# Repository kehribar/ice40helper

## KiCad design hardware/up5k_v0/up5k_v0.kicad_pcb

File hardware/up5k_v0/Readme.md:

# UP5K Development Board

TODO: Add details ...

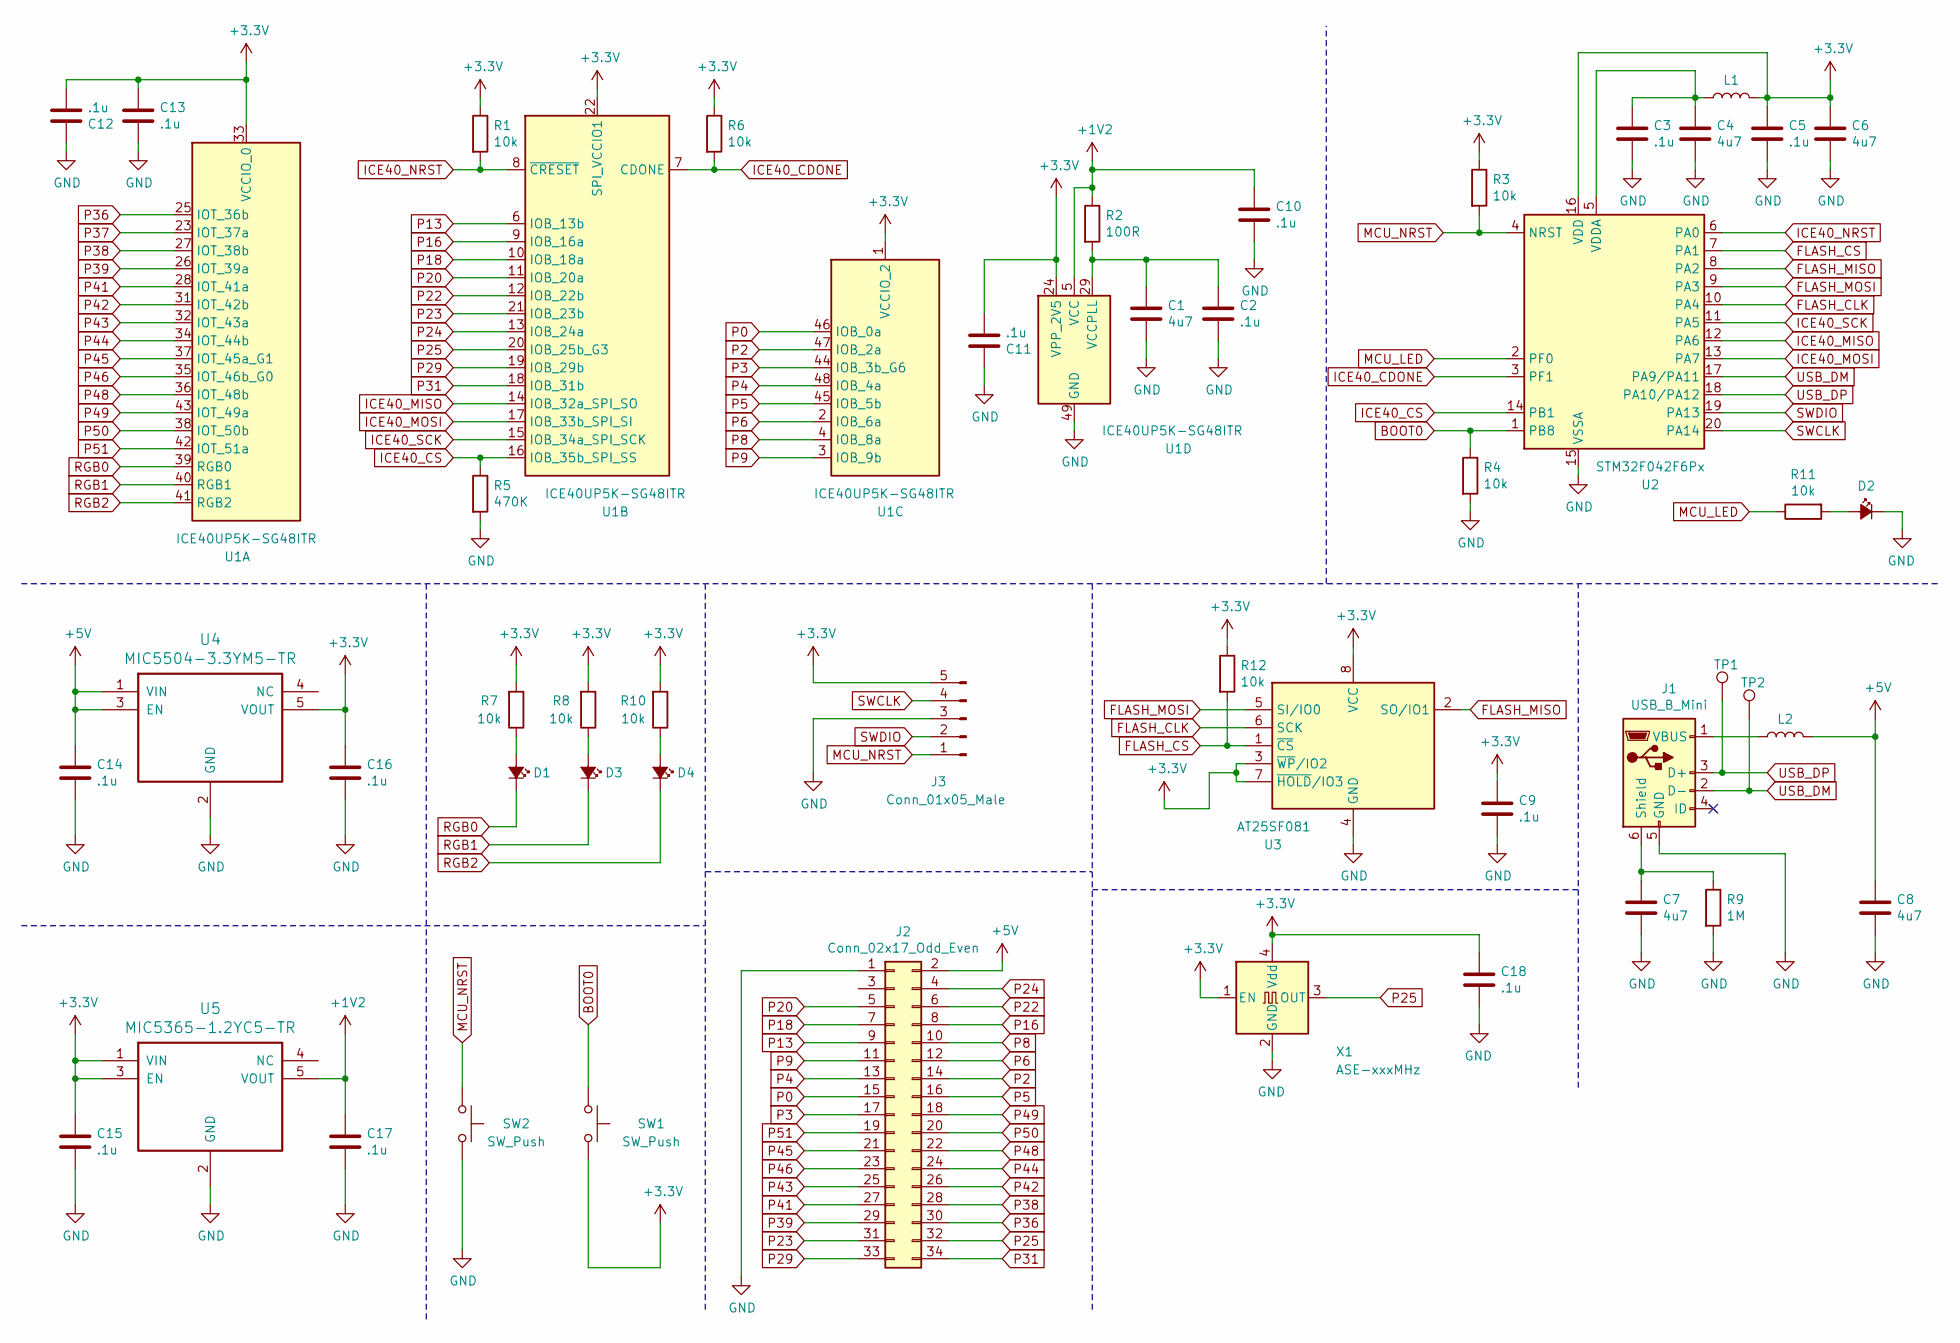
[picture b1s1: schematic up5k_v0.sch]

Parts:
C1, C4, C6, C7, C8: 4u7; C_0805_2012Metric
C2, C3, C5, C9, C10, C11, C12, C13, C14, C15, C16, C17, C18: .1u; C_0805_2012Metric
D1, D2, D3, D4: LED_Small_ALT; LED_0805_2012Metric_Castellated
J1: USB_B_Mini; USB_Micro-B_Molex_47346-0001
J2: Conn_02x17_Odd_Even; PinHeader_2x17_P2.54mm_Vertical
J3: Conn_01x05_Male; PinHeader_1x05_P2.54mm_Vertical
L1, L2: L; R_0805_2012Metric
R1, R3, R4, R6, R7, R8, R10, R11, R12: 10k; R_0805_2012Metric
R2: 100R; R_0805_2012Metric
R5: 470K; R_0805_2012Metric
R9: 1M; R_0805_2012Metric
SW1, SW2: SW_Push; PTS_810_SMT_Switch
TP1, TP2: TestPoint; TestPoint_Pad_1.5x1.5mm
U1: ICE40UP5K-SG48ITR; QFN-48-1EP_7x7mm_P0.5mm_EP5.6x5.6mm
U2: STM32F042F6Px; TSSOP-20_4.4x6.5mm_P0.65mm
U3: AT25SF081; SOIC-8_3.9x4.9mm_P1.27mm
U4: MIC5504-3.3YM5-TR; SOT-23-5_HandSoldering
U5: MIC5365-1.2YC5-TR; SOT-23-5_HandSoldering
X1: ASE-xxxMHz; Oscillator_SMD_Abracon_ASE-4Pin_3.2x2.5mm

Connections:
+1V2: C10.1, C17.1, R2.1, U1.5 (VCC), U1.30 (VCC), U5.5 (VOUT)
+3V3: C5.1, C6.1, C9.1, C11.2, C12.2, C13.1, C15.1, C16.1, C18.1, J3.5, L1.2, R1.1, R3.1, R6.1, R7.2, R8.2, R10.2, R12.1, SW1.2, U1.1 (VCCIO_2), U1.22 (SPI_VCCIO1), U1.24 (VPP_2V5), U1.33 (VCCIO_0), U2.16 (VDD), U3.3 (~WP~/IO2), U3.7 (~HOLD~/IO3), U3.8 (VCC), U4.5 (VOUT), U5.1 (VIN), U5.3 (EN), X1.1 (EN), X1.4 (Vdd)
+5V: C8.1, C14.1, J2.2, L2.2, U4.1 (VIN), U4.3 (EN)
BOOT0: R4.1, SW1.1, U2.1 (PB8)
FLASH_CLK: U2.10 (PA4), U3.6 (SCK)
FLASH_CS: R12.2, U2.7 (PA1), U3.1 (~CS)
FLASH_MISO: U2.8 (PA2), U3.2 (SO/IO1)
FLASH_MOSI: U2.9 (PA3), U3.5 (SI/IO0)
GND: C1.2, C2.2, C3.2, C4.2, C5.2, C6.2, C7.2, C8.2, C9.2, C10.2, C11.1, C12.1, C13.2, C14.2, C15.2, C16.2, C17.2, C18.2, D2.1 (K), J1.5 (GND), J2.1, J3.3, R4.2, R5.2, R9.2, SW2.2, U1.49 (GND), U2.15 (VSSA), U3.4 (GND), U4.2 (GND), U5.2 (GND), X1.2 (GND)
ICE40_CDONE: R6.2, U1.7 (CDONE), U2.3 (PF1)
ICE40_CS: R5.1, U1.16 (IOB_35b_SPI_SS), U2.14 (PB1)
ICE40_MISO: U1.14 (IOB_32a_SPI_SO), U2.12 (PA6)
ICE40_MOSI: U1.17 (IOB_33b_SPI_SI), U2.13 (PA7)
ICE40_NRST: R1.2, U1.8 (~CRESET), U2.6 (PA0)
ICE40_SCK: U1.15 (IOB_34a_SPI_SCK), U2.11 (PA5)
MCU_LED: R11.1, U2.2 (PF0)
MCU_NRST: J3.1, R3.2, SW2.1, U2.4 (NRST)
unnamed: C1.1, C2.1, R2.2, U1.29 (VCCPLL)
unnamed: C3.1, C4.1, L1.1, U2.5 (VDDA)
unnamed: C7.1, J1.6 (Shield), R9.1
unnamed: D1.2 (A), R7.1
unnamed: D2.2 (A), R11.2
unnamed: D3.2 (A), R8.1
unnamed: D4.2 (A), R10.1
unnamed: J1.1 (VBUS), L2.1
P0: J2.15, U1.46 (IOB_0a)
P2: J2.14, U1.47 (IOB_2a)
P3: J2.17, U1.44 (IOB_3b_G6)
P4: J2.13, U1.48 (IOB_4a)
P5: J2.16, U1.45 (IOB_5b)
P6: J2.12, U1.2 (IOB_6a)
P8: J2.10, U1.4 (IOB_8a)
P9: J2.11, U1.3 (IOB_9b)
P13: J2.9, U1.6 (IOB_13b)
P16: J2.8, U1.9 (IOB_16a)
P18: J2.7, U1.10 (IOB_18a)
P20: J2.5, U1.11 (IOB_20a)
P22: J2.6, U1.12 (IOB_22b)
P23: J2.31, U1.21 (IOB_23b)
P24: J2.4, U1.13 (IOB_24a)
P25: J2.32, U1.20 (IOB_25b_G3), X1.3 (OUT)
P29: J2.33, U1.19 (IOB_29b)
P31: J2.34, U1.18 (IOB_31b)
P36: J2.30, U1.25 (IOT_36b)
P37: U1.23 (IOT_37a)
P38: J2.28, U1.27 (IOT_38b)
P39: J2.29, U1.26 (IOT_39a)
P41: J2.27, U1.28 (IOT_41a)
P42: J2.26, U1.31 (IOT_42b)
P43: J2.25, U1.32 (IOT_43a)
P44: J2.24, U1.34 (IOT_44b)
P45: J2.21, U1.37 (IOT_45a_G1)
P46: J2.23, U1.35 (IOT_46b_G0)
P48: J2.22, U1.36 (IOT_48b)
P49: J2.18, U1.43 (IOT_49a)
P50: J2.20, U1.38 (IOT_50b)
P51: J2.19, U1.42 (IOT_51a)
RGB0: D1.1 (K), U1.39 (RGB0)
RGB1: D3.1 (K), U1.40 (RGB1)
RGB2: D4.1 (K), U1.41 (RGB2)
SWCLK: J3.4, U2.20 (PA14)
SWDIO: J3.2, U2.19 (PA13)
USB_DM: J1.2 (D-), TP2.1, U2.17 (PA9/PA11)
USB_DP: J1.3 (D+), TP1.1, U2.18 (PA10/PA12)

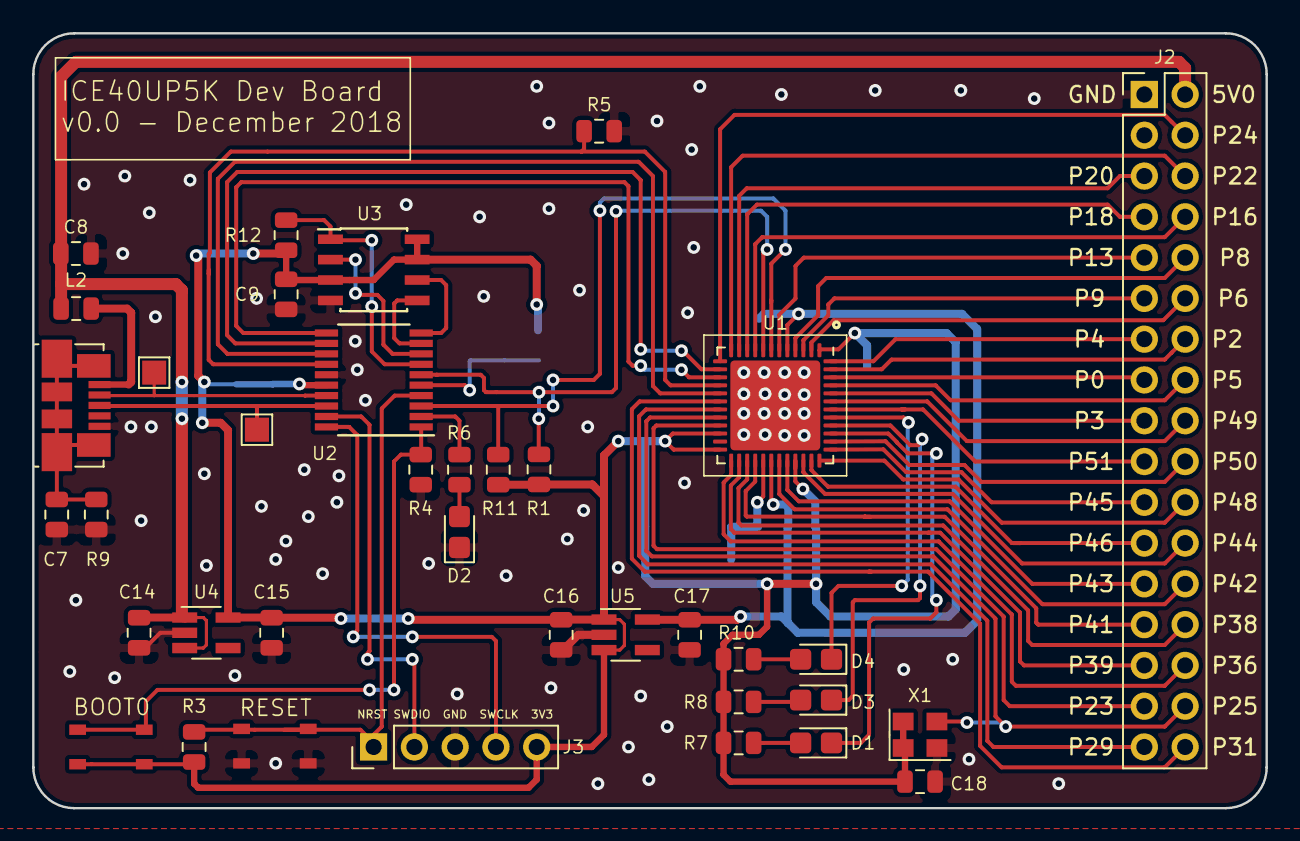
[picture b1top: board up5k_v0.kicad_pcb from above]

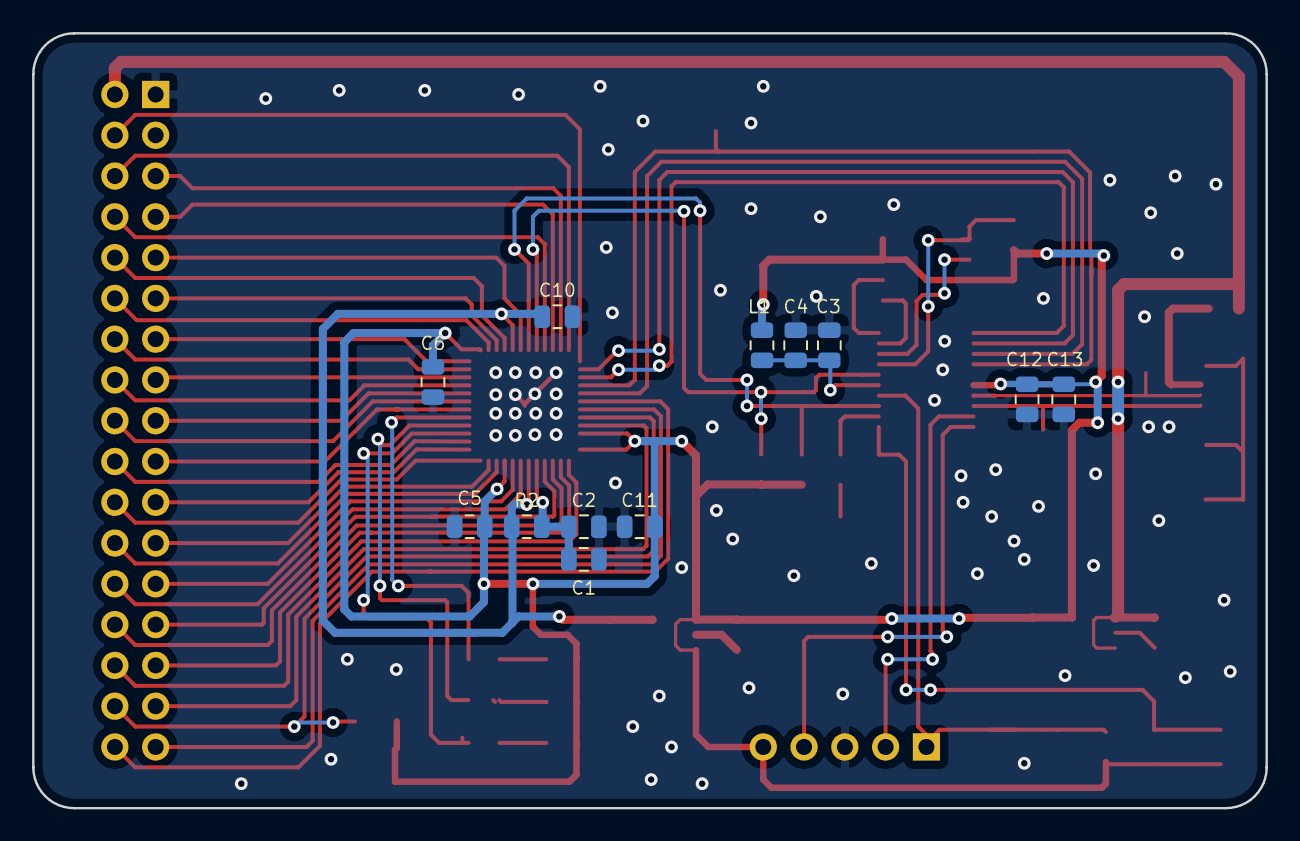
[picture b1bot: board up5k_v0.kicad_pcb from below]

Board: 2 copper layers, 76.8 x 48.3 mm, 49 parts (12 on the bottom side), 63 nets.

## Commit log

2018-11-23 Initial commit.
2018-11-23 Make SPI transfer generic.
2018-12-05 Non-volatile configuration support with SPI flash connected to STM32
2018-12-05 Wording fixes.
2018-12-05 new file: proto_v0.jpg
2018-12-05 modified: ../README.md
2018-12-16 Restructure FPGA section
2018-12-16 UP5K board initial commit.
2018-12-26 SPI flash interface changed from bitbang to hardware
2018-12-26 TSSOP20 package specific pin remapping
2018-12-26 Hardware modifications for up5k board
2018-12-26 Set LED high while executing a commmand
2018-12-26 Add dfu-util based mcu programming
2018-12-26 UP5K example
2018-12-26 Flash memory layout doc added
2019-01-01 Addded SPI read/write interface. Improved usb layer.
2019-01-01 SPI read/write example
2019-01-01 Cosmetic changes
2019-01-01 Change pnr tool
2019-01-01 memio example
2019-01-01 Convenience script
2019-01-08 Update readme with prototype image.
2019-01-08 Hardware multiplier example
2020-06-20 SPI core bugfix. Faster implementation (fMax = ~52 MHz)
2020-06-20 Small tweak makes timing estimate fMax = ~64 MHz
